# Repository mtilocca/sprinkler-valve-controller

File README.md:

# Sprinkler Valve Controller — ESP32-S3, 12 V in, 4 valves, isolated RS485

**Status:** Rev C (adds LoRa): schematic ERC clean, board routed and DRC clean (0 errors, 0 unconnected), fab files generated. Order in progress. This project is the simplified successor of the MPPT board (`../sprinkler-mppt-pcb`): PV and MPPT moved to a separate module.

## What it is

A small board that runs 4 sprinkler valves from a 12 V supply (battery, the PV/MPPT module, or a wall adapter; never above 15 V).

- **ESP32-S3-WROOM-1-N8**, firmware on Zephyr RTOS
- **4 valve outputs** (12 V, up to 1 A each, at most 2 on at once)
- **LoRa EU868** (Ebyte E22-900M22S, SX1262), single-channel gateway for your own sensors
- **WiFi and Bluetooth LE** from the ESP32-S3 module
- **Isolated RS485** (CA-IS3092W) for Modbus RTU
- **USB-C** for flashing, BOOT and RESET buttons, debug header, 4 LEDs
- **12 V monitor** into the ESP32 ADC, so the firmware can stop the valves on a low battery
- **Input protection:** resettable fuse, reverse-polarity P-FET, TVS

Target board: 100 × 60 mm, 2 layers, all SMT parts on the top, only screw terminals and headers through-hole.
Radio: Ebyte E22-900M22S (SX1262, EU 868 MHz) single-channel LoRa gateway radio with a u.FL antenna connector, see docs/08-fabrication.md (Rev C).

## Documents

| File | Content |
|------|---------|
| [docs/01-requirements.md](docs/01-requirements.md) | Requirements and assumptions |
| [docs/02-hardware.md](docs/02-hardware.md) | Power tree, valves, RS485, USB-C, protection |
| [docs/03-pinmap.md](docs/03-pinmap.md) | ESP32-S3 GPIO map |
| [docs/04-firmware.md](docs/04-firmware.md) | Firmware notes |
| [docs/06-bringup.md](docs/06-bringup.md) | Bring-up and test plan |
| [docs/07-parts-check.md](docs/07-parts-check.md) | Web check of the risky parts, LCSC numbers, risks |
| [docs/08-fabrication.md](docs/08-fabrication.md) | JLCPCB order settings, files, checks |
| [docs/09-shopping-list.md](docs/09-shopping-list.md) | Hand-soldered parts and other things to buy |
| [docs/10-board-layout.md](docs/10-board-layout.md) | Board layout, capabilities, layout rules, bring-up notes |
| [hardware/README.md](hardware/README.md) | How the schematic and board are generated |

## Schematic

PDF: [hardware/valve_controller_schematic.pdf](hardware/valve_controller_schematic.pdf). Generated from `hardware/valve_controller.py` (SKiDL); open `hardware/valve_controller.kicad_pro` in KiCad.

| Sheet | Content |
|-------|---------|
| `power_in` | 12 V terminal, fuse, reverse-polarity P-FET, TVS, 12 V monitor divider |
| `aux_power` | AP63205 5 V buck, USB 5 V OR, AMS1117-3.3 LDO (22 µF tantalum output) |
| `esp32` | ESP32-S3 module, BOOT and RESET, debug header |
| `usb_c` | USB-C connector, CC resistors, ESD protection |
| `lora` | E22-900M22S LoRa module, decoupling, u.FL antenna connector |
| `valves` | 4 × AO3400A drivers with flyback diodes, screw terminals, bulk capacitor |
| `rs485` | CA-IS3092W, TVS, termination and bias jumpers, terminal |
| `leds` | 4 LEDs and resistors |
| `test_points` | V12, 5V, 3V3, GND |

## Board

Open `hardware/valve_controller.kicad_pcb` (or the project `hardware/valve_controller.kicad_pro`) in KiCad 10. Layout notes: [docs/10-board-layout.md](docs/10-board-layout.md).

### 3D views

### Layout

Top side with silkscreen:

Both copper layers (red = top, blue = bottom, GND pours on both):

### Schematic sheets

The schematic is generated label-only (nets are connected by name, see `hardware/README.md`). Full PDF: [hardware/valve_controller_schematic.pdf](hardware/valve_controller_schematic.pdf).

| Sheet | Image |
|-------|-------|
| `power_in` |  |
| `aux_power` |  |
| `esp32` |  |
| `usb_c` |  |
| `valves` |  |
| `rs485` |  |
| `lora` |  |
| `leds` |  |
| `test_points` |  |

## Fabrication specs

| Item | Value |
|------|-------|
| Size | 100 x 60 mm, 4 x M3 mounting holes |
| Layers | 2, GND pour on both layers with stitching vias |
| Copper, finish | 1 oz, HASL lead-free (ENIG optional) |
| Track and space | 0.2 / 0.2 mm; V12 rail 1.0 mm, valve returns 0.6 mm, 5 V rails 0.5 mm |
| Vias | 0.6 / 0.3 mm |
| Antenna area | No copper in the strip at the top edge around the ESP32 antenna |
| RS485 isolation | Bus side right of the isolator: no GND pour, nothing under the chip body between the pin rows (about 7 mm) |
| Assembly | One side (top), SMT by JLCPCB; screw terminals and the debug header soldered by hand |
| Checks | ERC 0 violations; DRC 0 errors, 0 unconnected |

Files in `hardware/fab/`: `gerbers_valve_controller_RevC.zip` (and `gerber/`), `BOM_valve_controller.csv` (draft with suggested parts and rough prices), `BOM_JLCPCB_import.csv` (LCSC numbers to fill), `CPL_valve_controller.csv` (SMD positions, top side).

## Costs

**Rough estimates from memory, not quotes.** Upload the files to the JLCPCB quote page for real numbers. USD.

| Item | Estimate |
|------|----------|
| Components per board | about 14 (84 parts, 15 of the BOM lines are JLCPCB "extended" parts) |
| 5 bare 2-layer boards | about 2-8 |
| Shipping | 15-25 |
| JLCPCB SMT assembly fees (one side) | about 55-65 (setup, stencil, about 3 per extended part type) |
| **5 boards assembled by JLCPCB** (terminals and header soldered by hand) | **about 150-180, roughly 30-35 per board** |
| **2 boards assembled** | about 100-120 |
| **2 boards built entirely by hand** | about 50-70 (boards, shipping, parts) |

Open items before ordering: confirm stock and basic/extended class on the JLCPCB parts pages for the LCSC numbers in the BOM (see docs/07-parts-check.md), especially the LDO (low stock seen); the PTC fuse hold current drops when hot; two small silkscreen labels did not fit (RESET, BIAS B); terminal polarity labels are on the bottom side, next to the pads.

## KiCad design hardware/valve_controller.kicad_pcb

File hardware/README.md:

# hardware/

Generated design. Do not edit the `.kicad_sch` sheets by hand: edit `valve_controller.py` and regenerate.

```
python3 -m venv .venv && .venv/bin/pip install skidl      # once
.venv/bin/python valve_controller.py                        # netlist + label-only schematic
```

KiCad 10 (Flatpak): `flatpak run --command=kicad-cli org.kicad.KiCad sch erc ...` for ERC; PDF with `sch export pdf`.

| File | What |
|------|------|
| `valve_controller.py` | SKiDL design with datasheet pin assertions |
| `net2sch.py` | Netlist to label-only hierarchical schematic |
| `valve_custom.kicad_sym` | Local symbols: CA-IS3092W and a numbered P-FET (listed in `sym-lib-table`) |
| `valve_controller.kicad_pro` | Project, net classes: Power 1.0 mm (V12), Valve 0.6 mm, Rail 0.4 mm |
| `make_pcb.py`, `place_pcb.py`, `mini_route.py`, `add_gnd_pour.py`, `silk_cleanup.py`, `fab_prep.py`, `remove_dangling.py` | Layout helpers inherited from the MPPT board; to be adapted for the new 70 x 60 mm 2-layer layout |

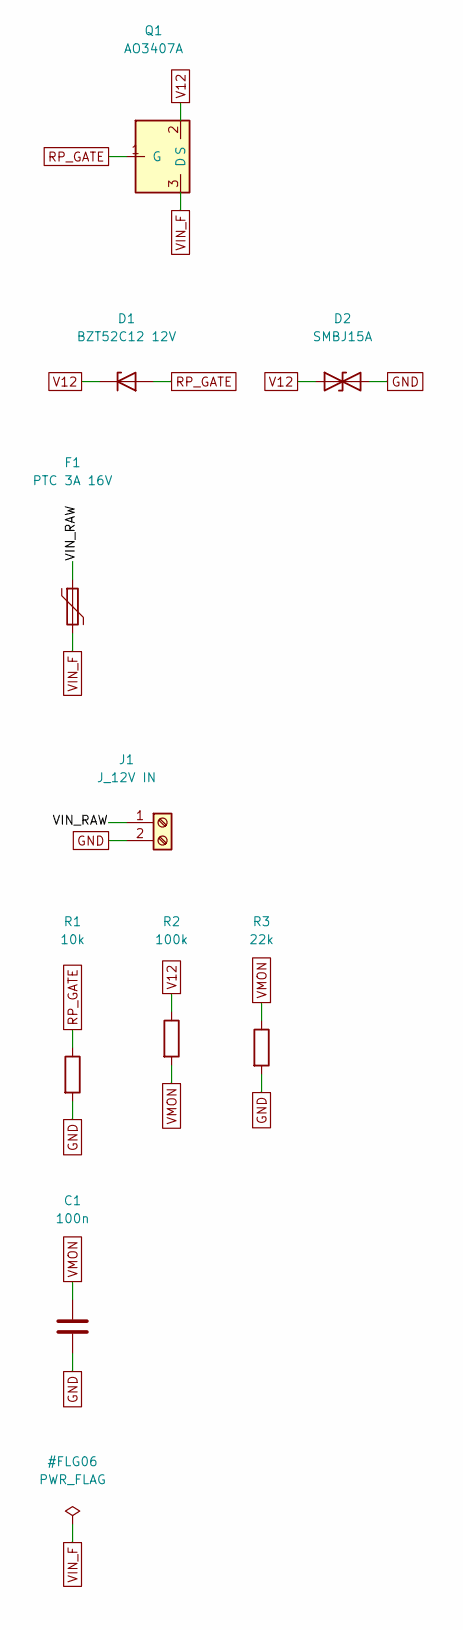
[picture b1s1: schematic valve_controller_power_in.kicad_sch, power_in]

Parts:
C1: 100n; C_0603_1608Metric
D1: BZT52C12 12V; D_SOD-123
D2: SMBJ15A; D_SMB
F1: PTC 3A 16V; Fuse_1812_4532Metric
J1: J_12V IN; TerminalBlock_Phoenix_MKDS-3-2-5.08_1x02_P5.08mm_Horizontal
Q1: AO3407A; SOT-23
R1: 10k; R_0603_1608Metric
R2: 100k; R_0603_1608Metric
R3: 22k; R_0603_1608Metric

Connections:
/power_in/VIN_RAW: F1.1, J1.1
GND: C1.2, D2.2 (A2), J1.2, R1.2, R3.2; also elsewhere on the board
RP_GATE: D1.2 (A), Q1.1 (G), R1.1; also elsewhere on the board
V12: D1.1 (K), D2.1 (A1), Q1.2 (S), R2.1; also elsewhere on the board
VIN_F: F1.2, Q1.3 (D); also elsewhere on the board
VMON: C1.1, R2.2, R3.1; also elsewhere on the board

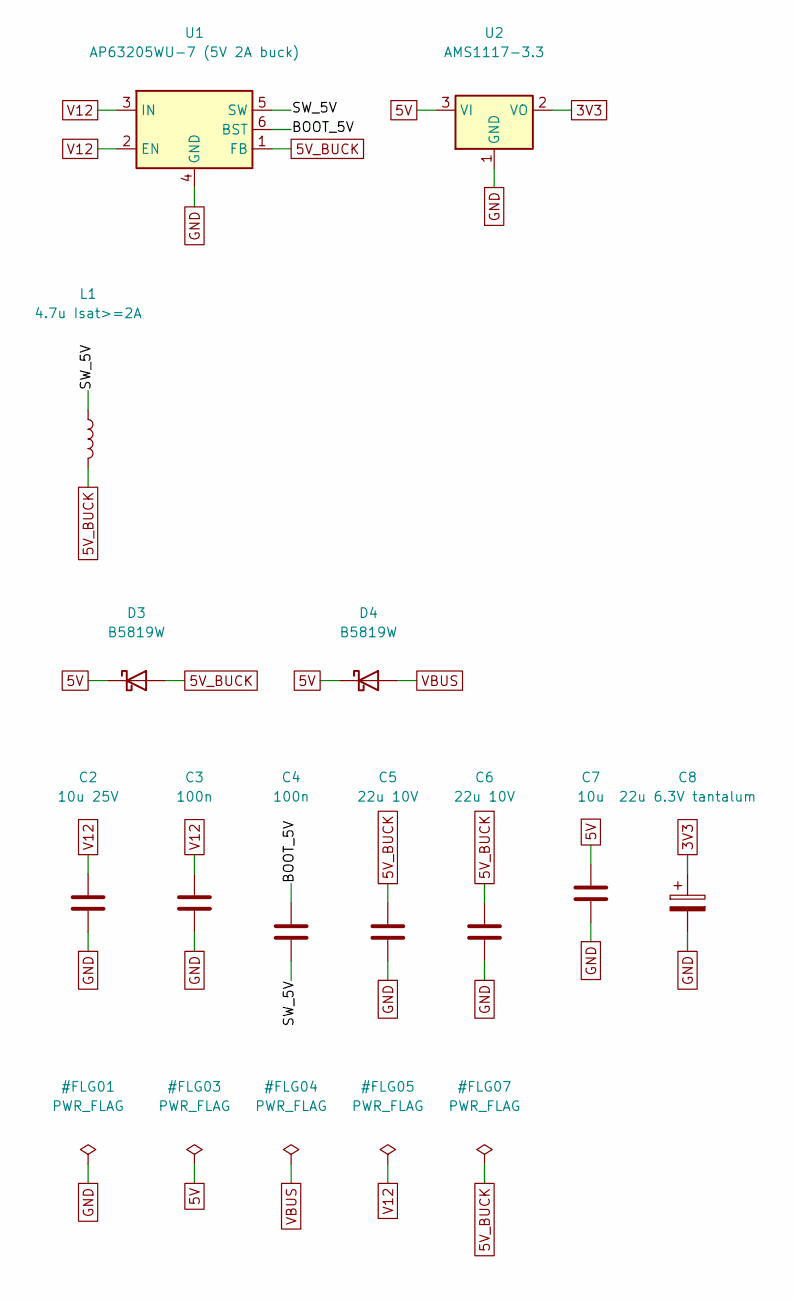
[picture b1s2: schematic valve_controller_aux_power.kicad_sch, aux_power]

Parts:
C2: 10u 25V; C_1206_3216Metric
C3, C4: 100n; C_0603_1608Metric
C5, C6: 22u 10V; C_1206_3216Metric
C7: 10u; C_1206_3216Metric
C8: 22u 6.3V tantalum; CP_EIA-3216-18_Kemet-A
D3, D4: B5819W; D_SOD-123
L1: 4.7u Isat>=2A; L_Bourns-SRN4018
U1: AP63205WU-7 (5V 2A buck); TSOT-23-6
U2: AMS1117-3.3; SOT-223-3_TabPin2

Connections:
3V3: C8.1, U2.2 (VO); also elsewhere on the board
5V: C7.1, D3.1 (K), D4.1 (K), U2.3 (VI); also elsewhere on the board
5V_BUCK: C5.1, C6.1, D3.2 (A), L1.2, U1.1 (FB); also elsewhere on the board
/aux_power/BOOT_5V: C4.1, U1.6 (BST)
/aux_power/SW_5V: C4.2, L1.1, U1.5 (SW)
GND: C2.2, C3.2, C5.2, C6.2, C7.2, C8.2, U1.4 (GND), U2.1 (GND); also elsewhere on the board
V12: C2.1, C3.1, U1.2 (EN), U1.3 (IN); also elsewhere on the board
VBUS: D4.2 (A); also elsewhere on the board

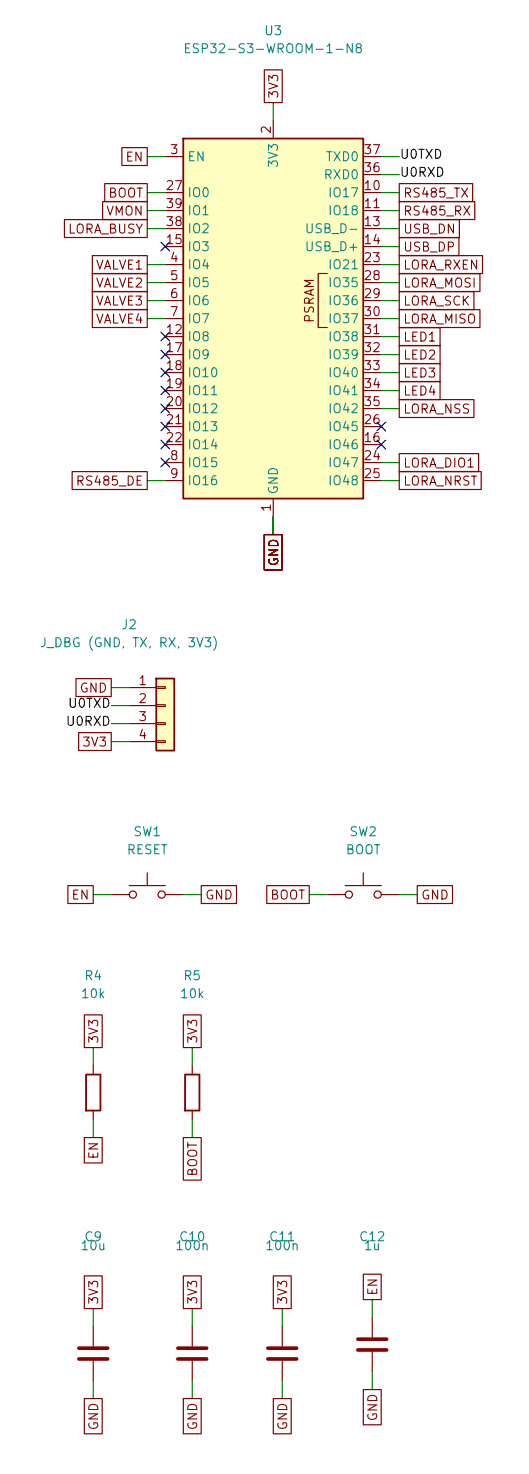
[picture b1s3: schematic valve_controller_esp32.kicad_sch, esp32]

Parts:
C9: 10u; C_1206_3216Metric
C10, C11: 100n; C_0603_1608Metric
C12: 1u; C_0603_1608Metric
J2: J_DBG (GND, TX, RX, 3V3); PinHeader_1x04_P2.54mm_Vertical
R4, R5: 10k; R_0603_1608Metric
SW1: RESET; SW_SPST_PTS645Sx43SMTR92
SW2: BOOT; SW_SPST_PTS645Sx43SMTR92
U3: ESP32-S3-WROOM-1-N8; ESP32-S3-WROOM-1

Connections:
3V3: C9.1, C10.1, C11.1, J2.4, R4.1, R5.1, U3.2 (3V3); also elsewhere on the board
/esp32/U0RXD: J2.3, U3.36 (RXD0)
/esp32/U0TXD: J2.2, U3.37 (TXD0)
BOOT: R5.2, SW2.1, U3.27 (IO0); also elsewhere on the board
EN: C12.1, R4.2, SW1.1, U3.3 (EN); also elsewhere on the board
GND: C9.2, C10.2, C11.2, C12.2, J2.1, SW1.2, SW2.2, U3.1 (GND), U3.40 (GND), U3.41 (GND); also elsewhere on the board
LED1: U3.31 (IO38); also elsewhere on the board
LED2: U3.32 (IO39); also elsewhere on the board
LED3: U3.33 (IO40); also elsewhere on the board
LED4: U3.34 (IO41); also elsewhere on the board
LORA_BUSY: U3.38 (IO2); also elsewhere on the board
LORA_DIO1: U3.24 (IO47); also elsewhere on the board
LORA_MISO: U3.30 (IO37); also elsewhere on the board
LORA_MOSI: U3.28 (IO35); also elsewhere on the board
LORA_NRST: U3.25 (IO48); also elsewhere on the board
LORA_NSS: U3.35 (IO42); also elsewhere on the board
LORA_RXEN: U3.23 (IO21); also elsewhere on the board
LORA_SCK: U3.29 (IO36); also elsewhere on the board
RS485_DE: U3.9 (IO16); also elsewhere on the board
RS485_RX: U3.11 (IO18); also elsewhere on the board
RS485_TX: U3.10 (IO17); also elsewhere on the board
USB_DN: U3.13 (USB_D-); also elsewhere on the board
USB_DP: U3.14 (USB_D+); also elsewhere on the board
VALVE1: U3.4 (IO4); also elsewhere on the board
VALVE2: U3.5 (IO5); also elsewhere on the board
VALVE3: U3.6 (IO6); also elsewhere on the board
VALVE4: U3.7 (IO7); also elsewhere on the board
VMON: U3.39 (IO1); also elsewhere on the board

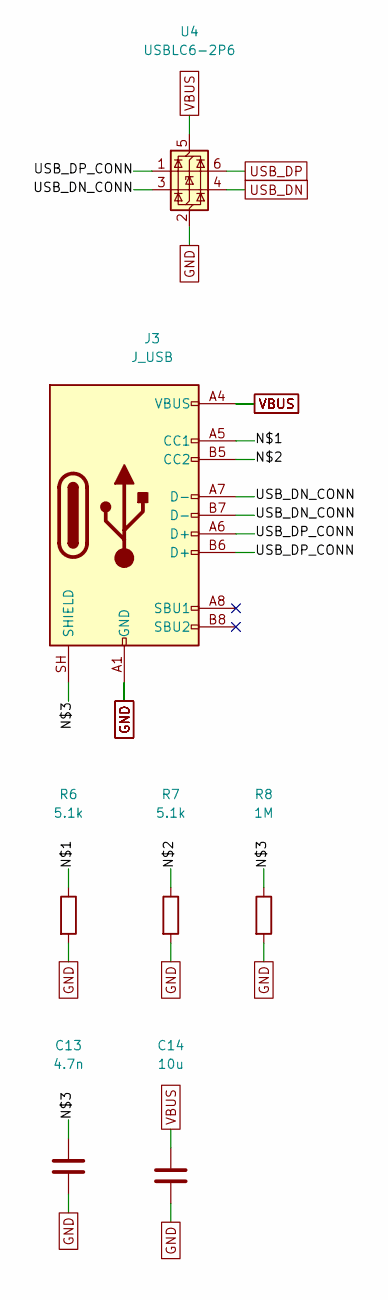
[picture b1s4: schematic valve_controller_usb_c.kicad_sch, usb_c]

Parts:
C13: 4.7n; C_0603_1608Metric
C14: 10u; C_1206_3216Metric
J3: J_USB; USB_C_Receptacle_HRO_TYPE-C-31-M-12
R6, R7: 5.1k; R_0603_1608Metric
R8: 1M; R_0603_1608Metric
U4: USBLC6-2P6; SOT-666

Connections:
/usb_c/N$1: J3.A5 (CC1), R6.1
/usb_c/N$2: J3.B5 (CC2), R7.1
/usb_c/N$3: C13.1, J3.SH (SHIELD), R8.1
/usb_c/USB_DN_CONN: J3.A7 (D-), J3.B7 (D-), U4.3 (I/O2)
/usb_c/USB_DP_CONN: J3.A6 (D+), J3.B6 (D+), U4.1 (I/O1)
GND: C13.2, C14.2, J3.A1 (GND), J3.A12 (GND), J3.B1 (GND), J3.B12 (GND), R6.2, R7.2, R8.2, U4.2 (GND); also elsewhere on the board
USB_DN: U4.4 (I/O2); also elsewhere on the board
USB_DP: U4.6 (I/O1); also elsewhere on the board
VBUS: C14.1, J3.A4 (VBUS), J3.A9 (VBUS), J3.B4 (VBUS), J3.B9 (VBUS), U4.5 (VBUS); also elsewhere on the board

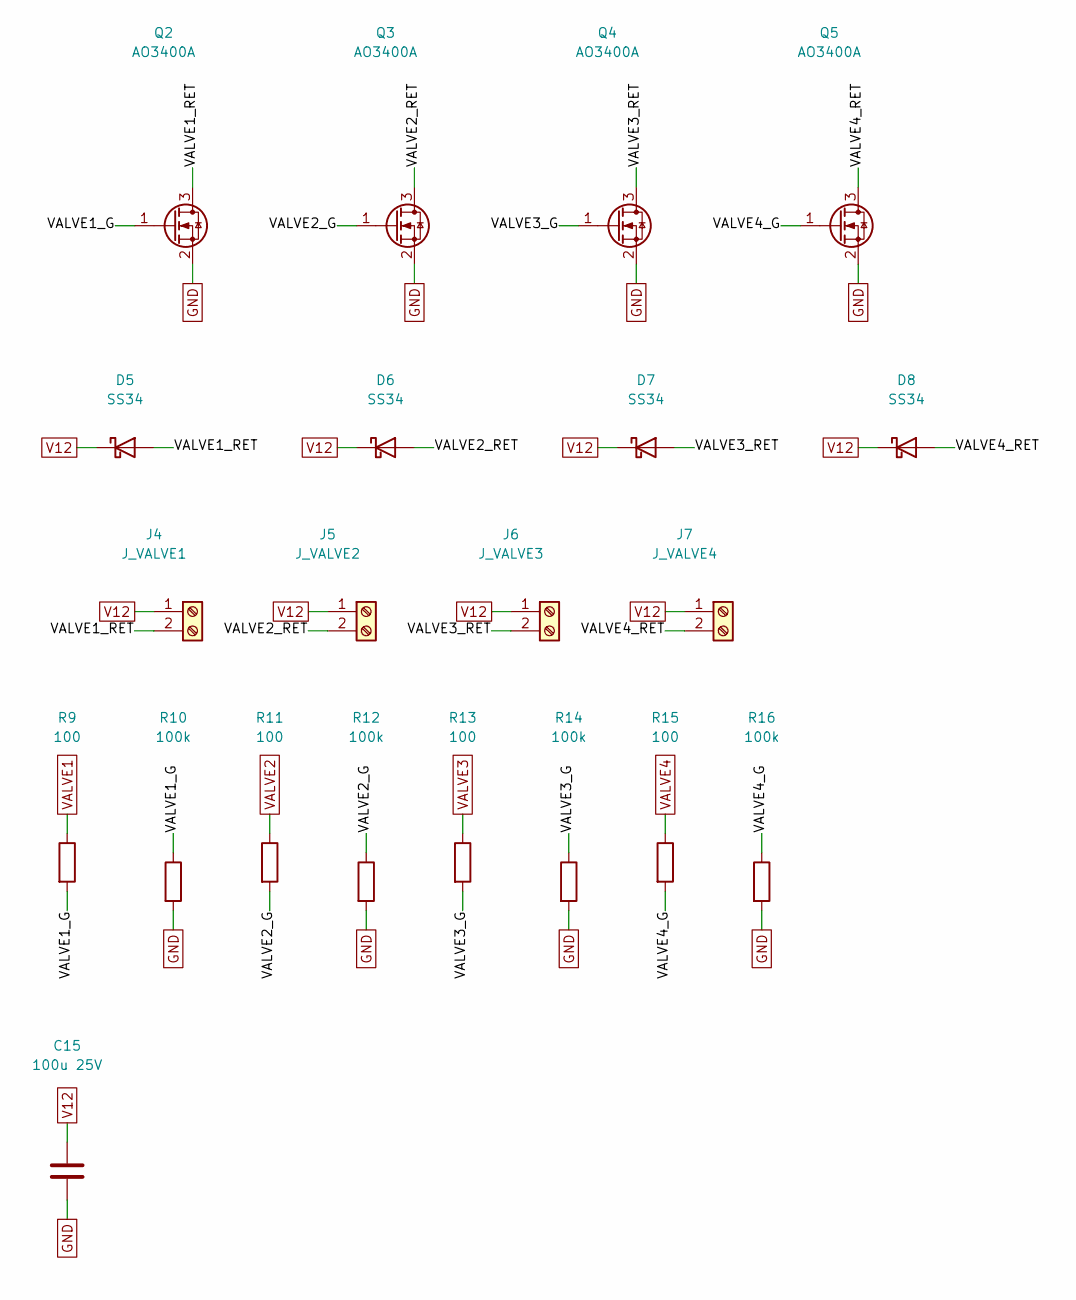
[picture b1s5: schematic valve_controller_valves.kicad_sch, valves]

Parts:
C15: 100u 25V; CP_Elec_6.3x7.7
D5, D6, D7, D8: SS34; D_SMA
J4: J_VALVE1; TerminalBlock_Phoenix_MKDS-1,5-2-5.08_1x02_P5.08mm_Horizont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
J5: J_VALVE2; TerminalBlock_Phoenix_MKDS-1,5-2-5.08_1x02_P5.08mm_Horizont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
J6: J_VALVE3; TerminalBlock_Phoenix_MKDS-1,5-2-5.08_1x02_P5.08mm_Horizont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
J7: J_VALVE4; TerminalBlock_Phoenix_MKDS-1,5-2-5.08_1x02_P5.08mm_Horizont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
Q2, Q3, Q4, Q5: AO3400A; SOT-23
R9, R11, R13, R15: 100; R_0603_1608Metric
R10, R12, R14, R16: 100k; R_0603_1608Metric

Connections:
/valves/VALVE1_G: Q2.1 (G), R9.2, R10.1
/valves/VALVE1_RET: D5.2 (A), J4.2, Q2.3 (D)
/valves/VALVE2_G: Q3.1 (G), R11.2, R12.1
/valves/VALVE2_RET: D6.2 (A), J5.2, Q3.3 (D)
/valves/VALVE3_G: Q4.1 (G), R13.2, R14.1
/valves/VALVE3_RET: D7.2 (A), J6.2, Q4.3 (D)
/valves/VALVE4_G: Q5.1 (G), R15.2, R16.1
/valves/VALVE4_RET: D8.2 (A), J7.2, Q5.3 (D)
GND: C15.2, Q2.2 (S), Q3.2 (S), Q4.2 (S), Q5.2 (S), R10.2, R12.2, R14.2, R16.2; also elsewhere on the board
V12: C15.1, D5.1 (K), D6.1 (K), D7.1 (K), D8.1 (K), J4.1, J5.1, J6.1, J7.1; also elsewhere on the board
VALVE1: R9.1; also elsewhere on the board
VALVE2: R11.1; also elsewhere on the board
VALVE3: R13.1; also elsewhere on the board
VALVE4: R15.1; also elsewhere on the board

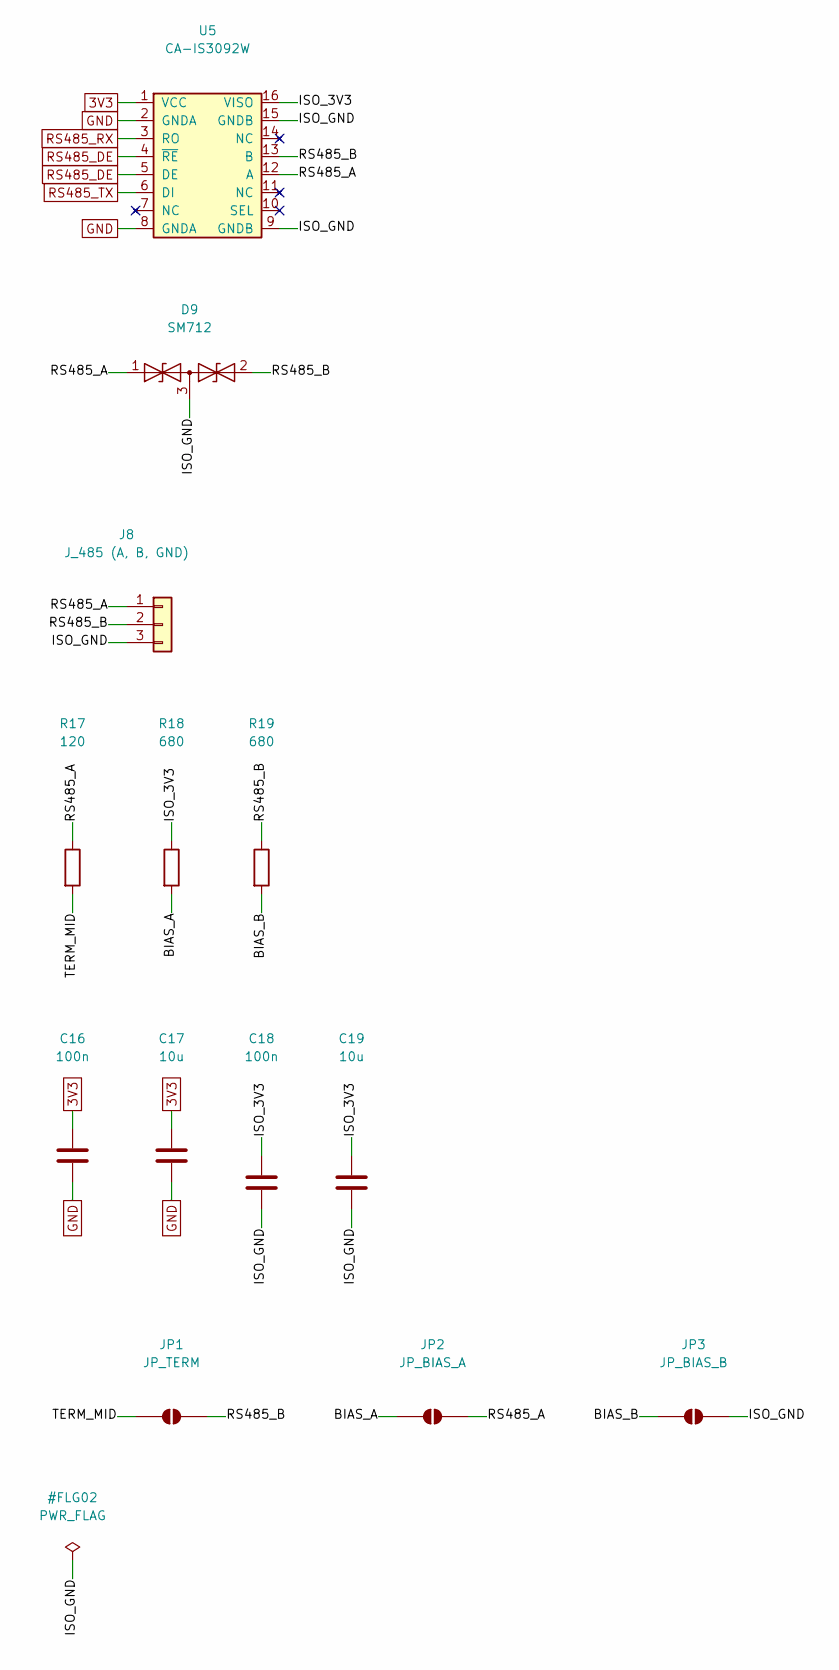
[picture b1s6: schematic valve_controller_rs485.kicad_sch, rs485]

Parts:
C16, C18: 100n; C_0603_1608Metric
C17, C19: 10u; C_1206_3216Metric
D9: SM712; SOT-23
J8: J_485 (A, B, GND); TerminalBlock_Phoenix_PT-1,5-3-3.5-H_1x03_P3.50mm_Horizontal
JP1: JP_TERM; SolderJumper-2_P1.3mm_Open_Pad1.0x1.5mm
JP2: JP_BIAS_A; SolderJumper-2_P1.3mm_Open_Pad1.0x1.5mm
JP3: JP_BIAS_B; SolderJumper-2_P1.3mm_Open_Pad1.0x1.5mm
R17: 120; R_0603_1608Metric
R18, R19: 680; R_0603_1608Metric
U5: CA-IS3092W; SOIC-16W_7.5x10.3mm_P1.27mm

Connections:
3V3: C16.1, C17.1, U5.1 (VCC); also elsewhere on the board
/rs485/BIAS_A: JP2.1 (A), R18.2
/rs485/BIAS_B: JP3.1 (A), R19.2
/rs485/ISO_3V3: C18.1, C19.1, R18.1, U5.16 (VISO)
/rs485/ISO_GND: C18.2, C19.2, D9.3 (common), J8.3, JP3.2 (B), U5.9 (GNDB), U5.15 (GNDB)
/rs485/RS485_A: D9.1 (A1), J8.1, JP2.2 (B), R17.1, U5.12 (A)
/rs485/RS485_B: D9.2 (A2), J8.2, JP1.2 (B), R19.1, U5.13 (B)
/rs485/TERM_MID: JP1.1 (A), R17.2
GND: C16.2, C17.2, U5.2 (GNDA), U5.8 (GNDA); also elsewhere on the board
RS485_DE: U5.4 (~RE), U5.5 (DE); also elsewhere on the board
RS485_RX: U5.3 (RO); also elsewhere on the board
RS485_TX: U5.6 (DI); also elsewhere on the board

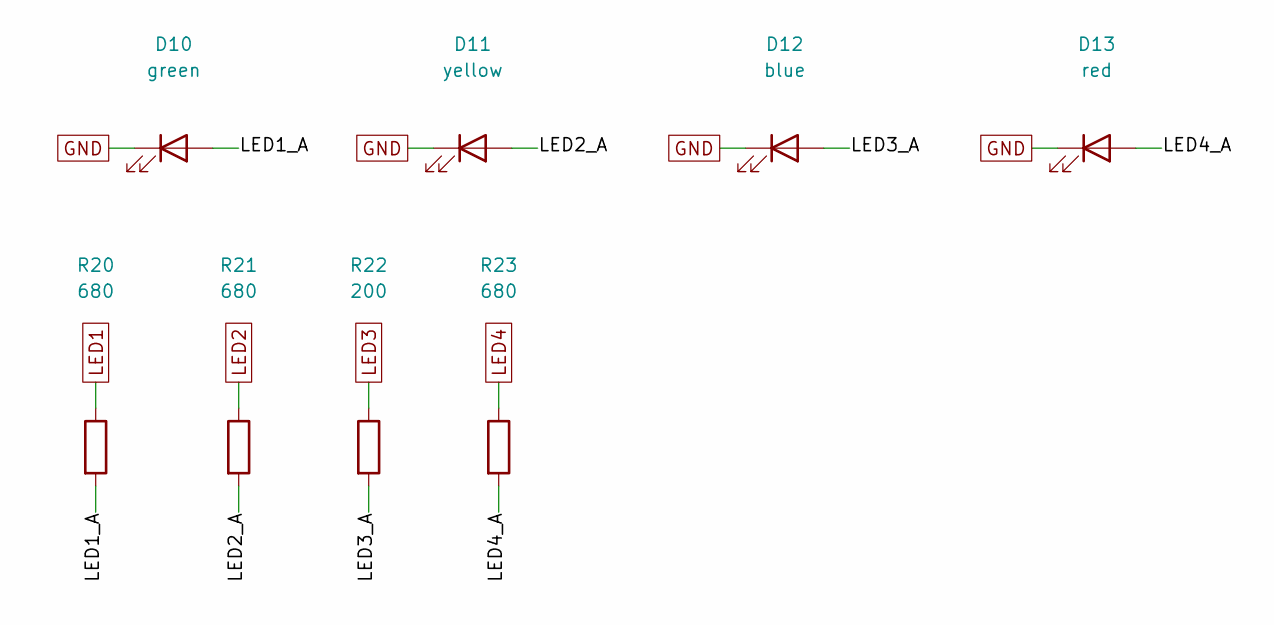
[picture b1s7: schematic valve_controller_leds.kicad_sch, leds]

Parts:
D10: green; LED_0603_1608Metric
D11: yellow; LED_0603_1608Metric
D12: blue; LED_0603_1608Metric
D13: red; LED_0603_1608Metric
R20, R21, R23: 680; R_0603_1608Metric
R22: 200; R_0603_1608Metric

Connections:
/leds/LED1_A: D10.2 (A), R20.2
/leds/LED2_A: D11.2 (A), R21.2
/leds/LED3_A: D12.2 (A), R22.2
/leds/LED4_A: D13.2 (A), R23.2
GND: D10.1 (K), D11.1 (K), D12.1 (K), D13.1 (K); also elsewhere on the board
LED1: R20.1; also elsewhere on the board
LED2: R21.1; also elsewhere on the board
LED3: R22.1; also elsewhere on the board
LED4: R23.1; also elsewhere on the board

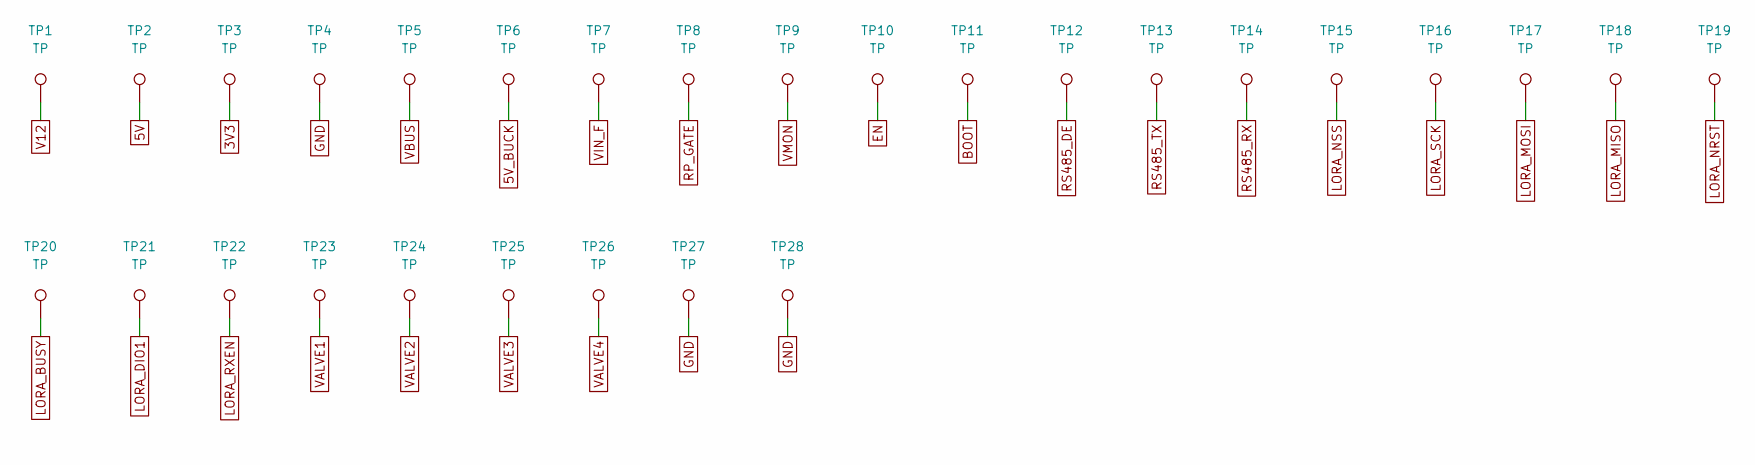
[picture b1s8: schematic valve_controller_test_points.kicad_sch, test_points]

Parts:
TP1, TP2, TP3, TP4: TP; TestPoint_Pad_D1.5mm
TP5, TP6, TP7, TP8, TP9, TP10, TP11, TP12, TP13, TP14, TP15, TP16, TP17, TP18, TP19, TP20, TP21, TP22, TP23, TP24, TP25, TP26, TP27, TP28: TP; TestPoint_Pad_D1.0mm

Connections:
3V3: TP3.1; also elsewhere on the board
5V: TP2.1; also elsewhere on the board
5V_BUCK: TP6.1; also elsewhere on the board
BOOT: TP11.1; also elsewhere on the board
EN: TP10.1; also elsewhere on the board
GND: TP4.1, TP27.1, TP28.1; also elsewhere on the board
LORA_BUSY: TP20.1; also elsewhere on the board
LORA_DIO1: TP21.1; also elsewhere on the board
LORA_MISO: TP18.1; also elsewhere on the board
LORA_MOSI: TP17.1; also elsewhere on the board
LORA_NRST: TP19.1; also elsewhere on the board
LORA_NSS: TP15.1; also elsewhere on the board
LORA_RXEN: TP22.1; also elsewhere on the board
LORA_SCK: TP16.1; also elsewhere on the board
RP_GATE: TP8.1; also elsewhere on the board
RS485_DE: TP12.1; also elsewhere on the board
RS485_RX: TP14.1; also elsewhere on the board
RS485_TX: TP13.1; also elsewhere on the board
V12: TP1.1; also elsewhere on the board
VALVE1: TP23.1; also elsewhere on the board
VALVE2: TP24.1; also elsewhere on the board
VALVE3: TP25.1; also elsewhere on the board
VALVE4: TP26.1; also elsewhere on the board
VBUS: TP5.1; also elsewhere on the board
VIN_F: TP7.1; also elsewhere on the board
VMON: TP9.1; also elsewhere on the board

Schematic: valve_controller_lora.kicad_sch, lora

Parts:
C20: 10u; C_1206_3216Metric
C21, C22: 100n; C_0603_1608Metric
J9: J_ANT (u.FL); U.FL_Hirose_U.FL-R-SMT-1_Vertical
U6: E22-900M22S

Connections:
3V3: C20.1, C21.1, C22.1, U6.9 (VCC); also elsewhere on the board
/lora/LORA_ANT: J9.1 (In), U6.21 (ANT)
/lora/LORA_TXEN: U6.7 (TXEN), U6.8 (DIO2)
GND: C20.2, C21.2, C22.2, J9.2 (Ext), U6.1 (GND), U6.2 (GND), U6.3 (GND), U6.4 (GND), U6.5 (GND), U6.10 (GND), U6.11 (GND), U6.12 (GND), U6.20 (GND), U6.22 (GND); also elsewhere on the board
LORA_BUSY: U6.14 (BUSY); also elsewhere on the board
LORA_DIO1: U6.13 (DIO1); also elsewhere on the board
LORA_MISO: U6.16 (MISO); also elsewhere on the board
LORA_MOSI: U6.17 (MOSI); also elsewhere on the board
LORA_NRST: U6.15 (NRST); also elsewhere on the board
LORA_NSS: U6.19 (NSS); also elsewhere on the board
LORA_RXEN: U6.6 (RXEN); also elsewhere on the board
LORA_SCK: U6.18 (SCK); also elsewhere on the board

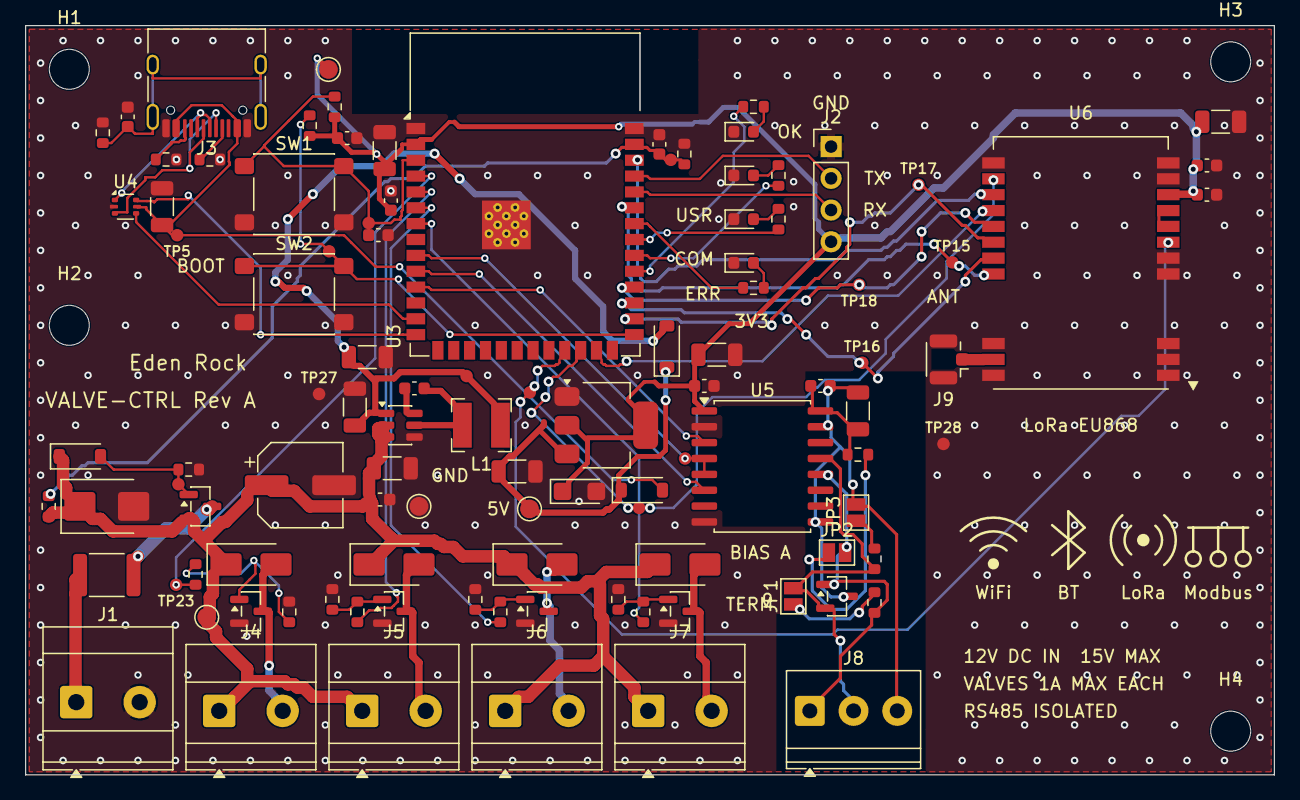
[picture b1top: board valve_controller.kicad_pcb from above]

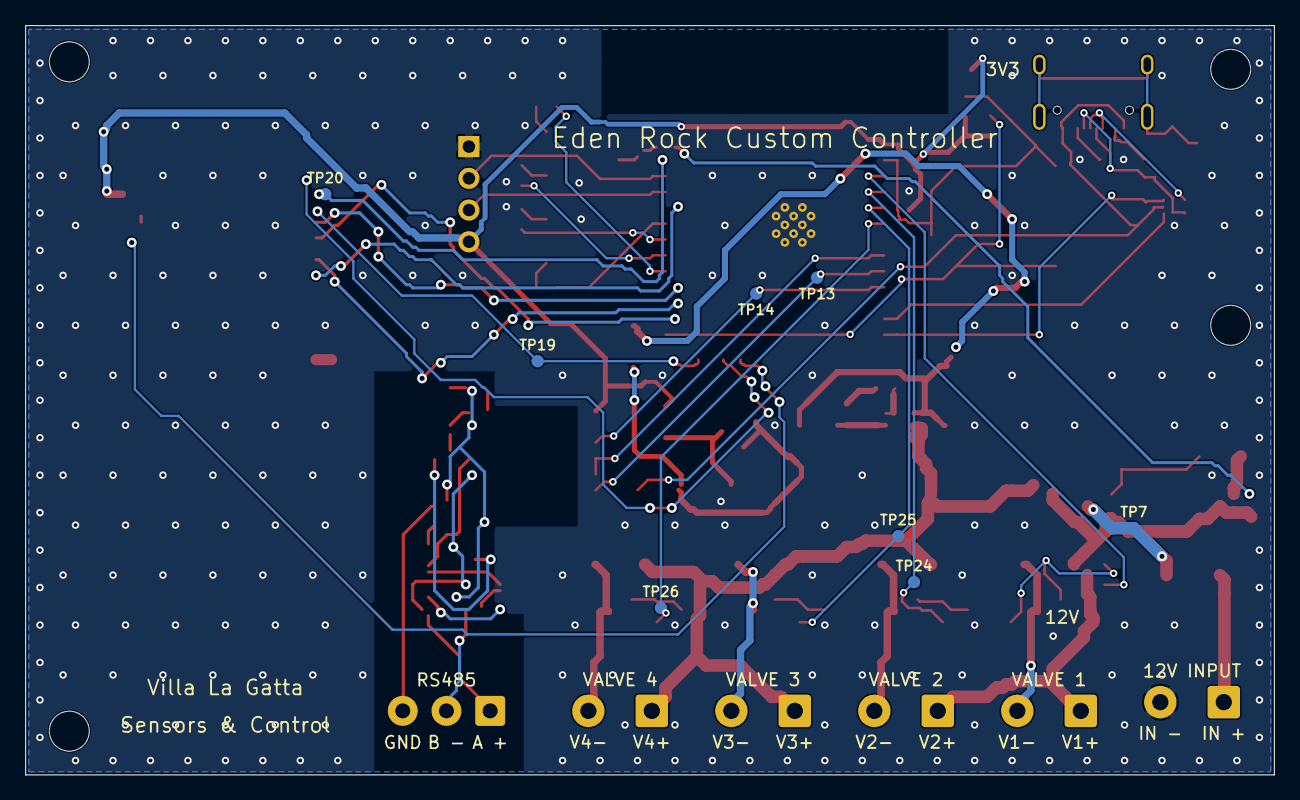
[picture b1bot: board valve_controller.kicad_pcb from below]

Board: 2 copper layers, 100.0 x 60.0 mm, 117 parts (8 on the bottom side), 63 nets.

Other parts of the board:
H1, H2, H3: M3; MountingHole_3.2mm_M3
H4: MountingHole_3.2mm_M3

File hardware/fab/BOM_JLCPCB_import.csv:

Comment,Designator,Footprint,LCSC Part #
100n,"C1,C3,C4,C10,C11,C16,C18,C21,C22",C_0603_1608Metric,C14663
10u 25V,C2,C_1206_3216Metric,C13585
22u 10V,"C5,C6",C_1206_3216Metric,C12891
10u,"C7,C9,C14,C17,C19,C20",C_1206_3216Metric,C13585
22u 6.3V tantalum,C8,CP_EIA-3216-18_Kemet-A,C11366
1u,C12,C_0603_1608Metric,C15849
4.7n,C13,C_0603_1608Metric,C53987
100u 25V,C15,CP_Elec_6.3x7.7,C72478
BZT52C12 12V,D1,D_SOD-123,C19077410
SMBJ15A,D2,D_SMB,C188412
B5819W,"D3,D4",D_SOD-123,C64885
SS34,"D5,D6,D7,D8",D_SMA,C8678
SM712,D9,SOT-23,C5364052
green,D10,LED_0603_1608Metric,C12624
yellow,D11,LED_0603_1608Metric,C2287
blue,D12,LED_0603_1608Metric,C2288
red,D13,LED_0603_1608Metric,C2286
PTC 3A 16V,F1,Fuse_1812_4532Metric,C6851473
J_USB,J3,USB_C_Receptacle_HRO_TYPE-C-31-M-12,C165948
J_ANT (u.FL),J9,U.FL_Hirose_U.FL-R-SMT-1_Vertical,C88374
4.7u Isat>=2A,L1,L_Bourns-SRN4018,C167806
AO3407A,Q1,SOT-23,C347478
AO3400A,"Q2,Q3,Q4,Q5",SOT-23,C20917
10k,"R1,R4,R5",R_0603_1608Metric,C25804
100k,"R2,R10,R12,R14,R16",R_0603_1608Metric,C25803
22k,R3,R_0603_1608Metric,C31850
5.1k,"R6,R7",R_0603_1608Metric,C23186
1M,R8,R_0603_1608Metric,C22935
100,"R9,R11,R13,R15",R_0603_1608Metric,C22775
120,R17,R_0603_1608Metric,C22787
680,"R18,R19,R20,R21,R23",R_0603_1608Metric,C23228
200,R22,R_0603_1608Metric,C8218
RESET,SW1,SW_SPST_PTS645Sx43SMTR92,C221880
BOOT,SW2,SW_SPST_PTS645Sx43SMTR92,C221880
AP63205WU-7 (5V 2A buck),U1,TSOT-23-6,C2071056
AMS1117-3.3,U2,SOT-223-3_TabPin2,C6186
ESP32-S3-WROOM-1-N8,U3,ESP32-S3-WROOM-1,C2913198
USBLC6-2P6,U4,SOT-666,C2827693
CA-IS3092W,U5,SOIC-16W_7.5x10.3mm_P1.27mm,C2890051
E22-900M22S,U6,E22-900M22S,C411293

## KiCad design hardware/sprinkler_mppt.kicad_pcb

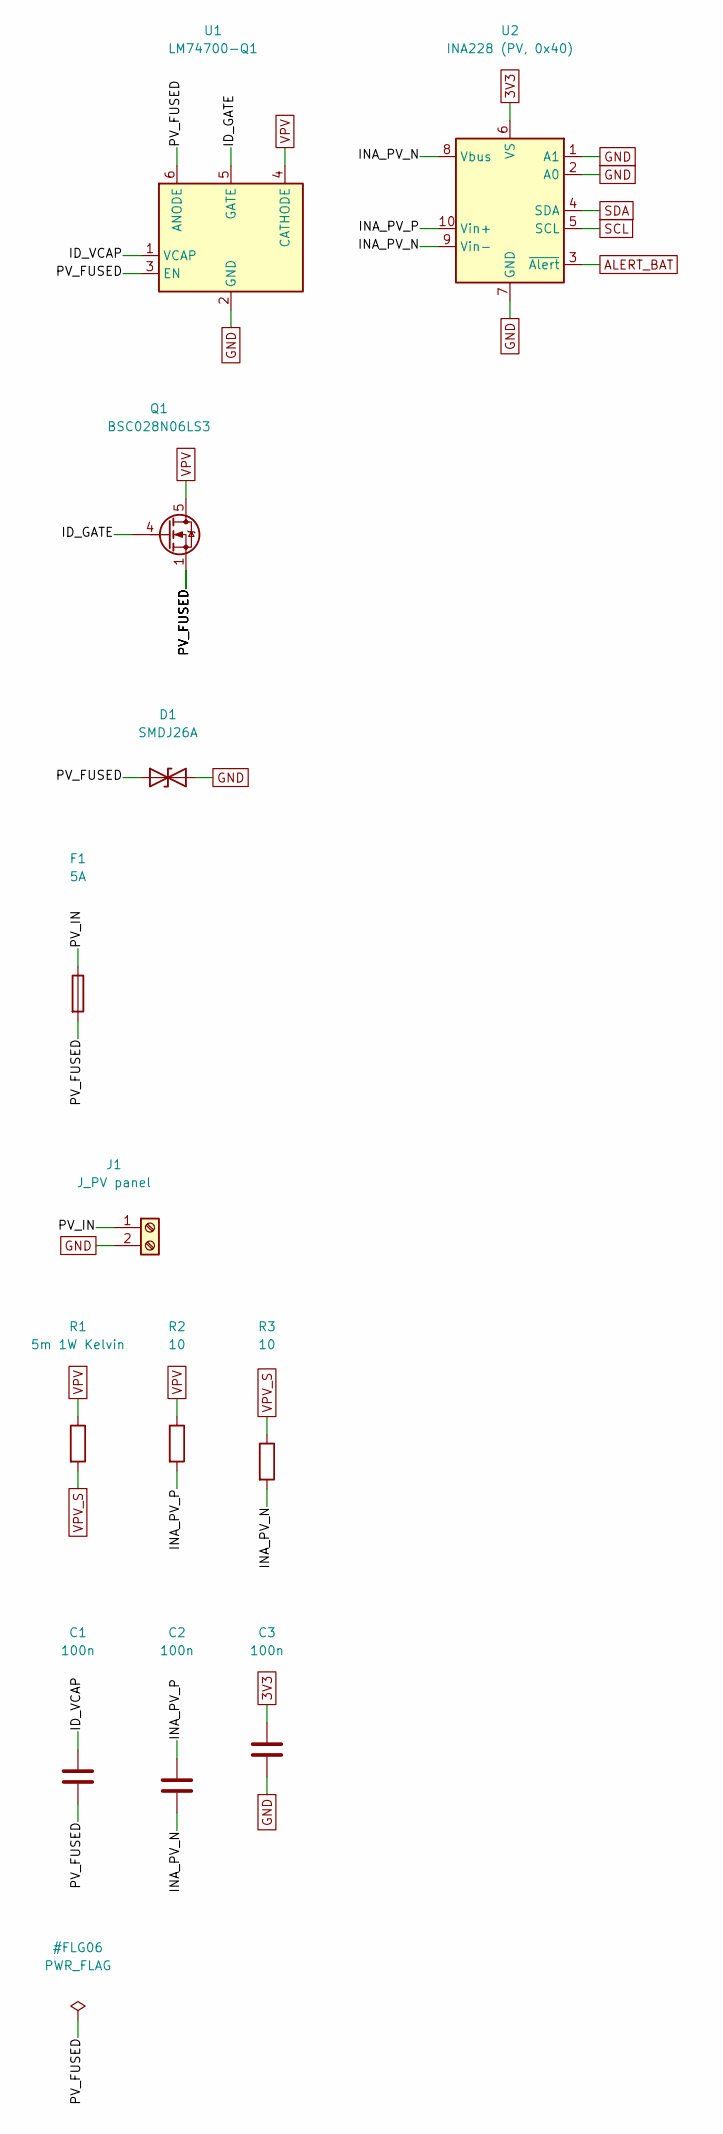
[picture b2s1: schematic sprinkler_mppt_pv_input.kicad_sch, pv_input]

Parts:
C1, C2, C3: 100n; C_0603_1608Metric
D1: SMDJ26A; D_SMC
F1: 5A; Fuse_1812_4532Metric
J1: J_PV panel; TerminalBlock_Phoenix_MKDS-3-2-5.08_1x02_P5.08mm_Horizontal
Q1: BSC028N06LS3; TDSON-8-1
R1: 5m 1W Kelvin; R_2512_6332Metric
R2, R3: 10; R_0603_1608Metric
U1: LM74700-Q1; SOT-23-6
U2: INA228 (PV, 0x40); TSSOP-10_3x3mm_P0.5mm

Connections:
3V3: C3.1, U2.6 (VS); also elsewhere on the board
/pv_input/ID_GATE: Q1.4 (G), U1.5 (GATE)
/pv_input/ID_VCAP: C1.1, U1.1 (VCAP)
/pv_input/INA_PV_N: C2.2, R3.2, U2.8 (Vbus), U2.9 (Vin-)
/pv_input/INA_PV_P: C2.1, R2.2, U2.10 (Vin+)
/pv_input/PV_FUSED: C1.2, D1.1 (A1), F1.2, Q1.1 (S), Q1.2 (S), Q1.3 (S), U1.3 (EN), U1.6 (ANODE)
/pv_input/PV_IN: F1.1, J1.1
ALERT_BAT: U2.3 (~Alert); also elsewhere on the board
GND: C3.2, D1.2 (A2), J1.2, U1.2 (GND), U2.1 (A1), U2.2 (A0), U2.7 (GND); also elsewhere on the board
SCL: U2.5 (SCL); also elsewhere on the board
SDA: U2.4 (SDA); also elsewhere on the board
VPV: Q1.5 (D), R1.1, R2.1, U1.4 (CATHODE); also elsewhere on the board
VPV_S: R1.2, R3.1; also elsewhere on the board

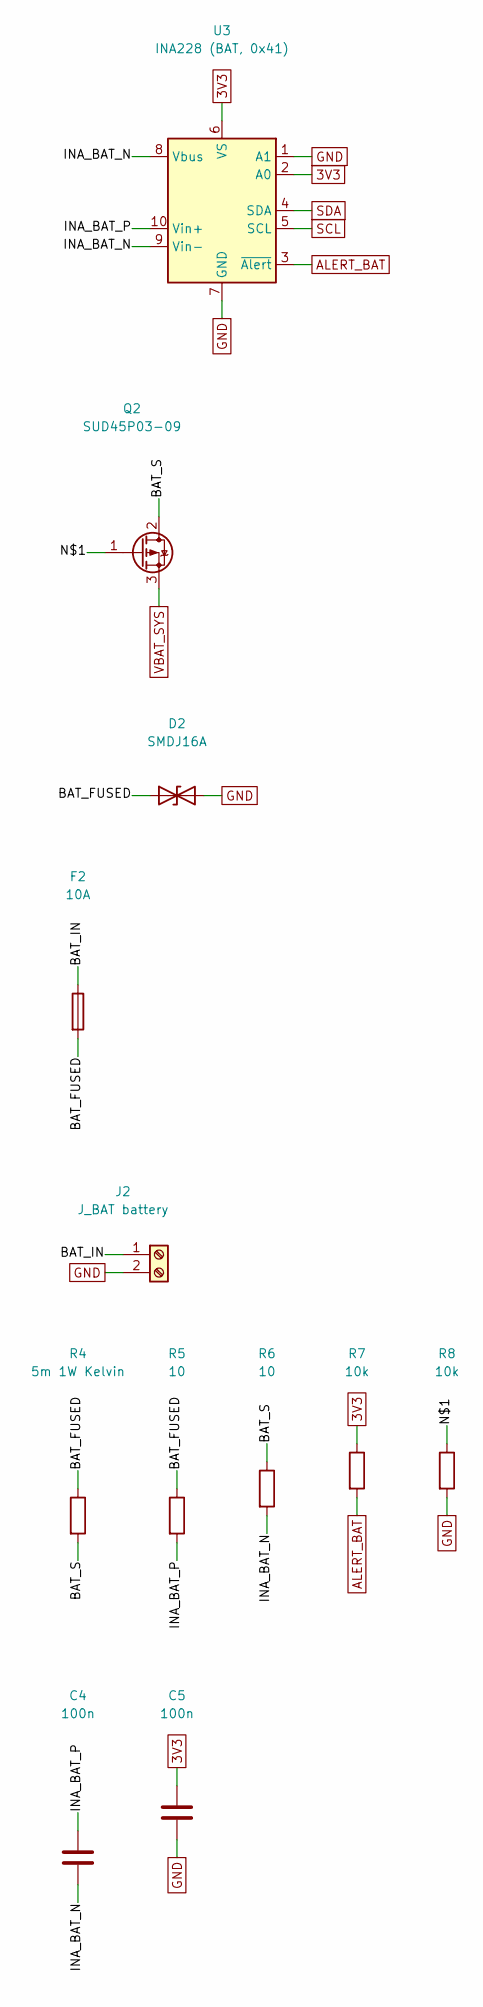
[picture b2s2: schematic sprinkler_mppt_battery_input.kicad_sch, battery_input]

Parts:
C4, C5: 100n; C_0603_1608Metric
D2: SMDJ16A; D_SMC
F2: 10A; Fuse_1812_4532Metric
J2: J_BAT battery; TerminalBlock_Phoenix_MKDS-3-2-5.08_1x02_P5.08mm_Horizontal
Q2: SUD45P03-09; TO-252-2
R4: 5m 1W Kelvin; R_2512_6332Metric
R5, R6: 10; R_0603_1608Metric
R7, R8: 10k; R_0603_1608Metric
U3: INA228 (BAT, 0x41); TSSOP-10_3x3mm_P0.5mm

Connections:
3V3: C5.1, R7.1, U3.2 (A0), U3.6 (VS); also elsewhere on the board
/battery_input/BAT_FUSED: D2.1 (A1), F2.2, R4.1, R5.1
/battery_input/BAT_IN: F2.1, J2.1
/battery_input/BAT_S: Q2.2 (D), R4.2, R6.1
/battery_input/INA_BAT_N: C4.2, R6.2, U3.8 (Vbus), U3.9 (Vin-)
/battery_input/INA_BAT_P: C4.1, R5.2, U3.10 (Vin+)
/battery_input/N$1: Q2.1 (G), R8.1
ALERT_BAT: R7.2, U3.3 (~Alert); also elsewhere on the board
GND: C5.2, D2.2 (A2), J2.2, R8.2, U3.1 (A1), U3.7 (GND); also elsewhere on the board
SCL: U3.5 (SCL); also elsewhere on the board
SDA: U3.4 (SDA); also elsewhere on the board
VBAT_SYS: Q2.3 (S); also elsewhere on the board
